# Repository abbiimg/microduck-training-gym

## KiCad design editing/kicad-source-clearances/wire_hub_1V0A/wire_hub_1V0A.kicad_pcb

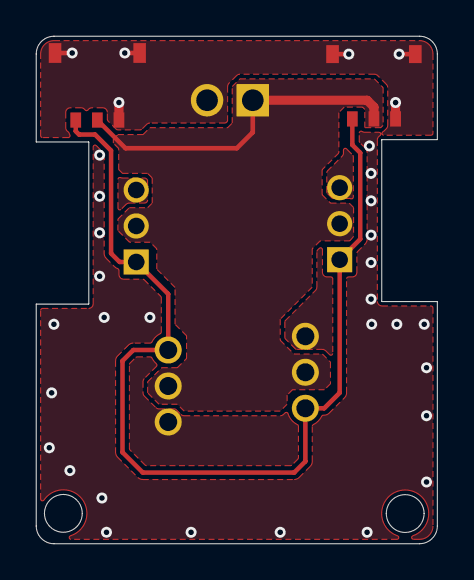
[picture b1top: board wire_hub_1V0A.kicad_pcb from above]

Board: 2 copper layers, 22.3 x 28.2 mm, 7 parts (0 on the bottom side), 3 nets.

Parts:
CN1: DB125-2.54-2P-GN-S; CN1
J1: HC-1.2-3PWT; J1
J2: BM03B-ACHSS-GAN-ETF(LF)(SN); J2
J3: A2007WR-3P; J3
J4: A2007WR-3P; J4
J5: A2007WV-3P; J5
J6: A2007WV-3P; J6

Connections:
/Battery: CN1.1, J1.2, J2.2, J3.2, J4.2, J5.2, J6.2
/DXL_BUS: J1.3, J2.3, J3.1, J4.1, J5.1, J6.1
/GND: CN1.2, J1.1, J1.4, J1.5, J2.1, J2.4, J2.5, J3.3, J4.3, J5.3, J6.3

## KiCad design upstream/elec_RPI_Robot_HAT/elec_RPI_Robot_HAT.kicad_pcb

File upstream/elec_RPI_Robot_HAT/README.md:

# "RPI_Robot_HAT" Electronic Board

> "RPI_Robot_HAT" is a raspberry pi HAT designed for small/medium size robots. It has an IMU, Dynamixel connectors and audio. Its size fits a Raspberry PI zero.

The RPI_Robot_HAT gathers:

- **IMU** over I2C + data fusion
- **Dynamixel motor communication**: both TTL and 485 to drive Dynamixel/Feetech motor (requires cable adaptation)
- **in/out audio device** with an integrated mems microphone. Wago connectors allows connection of loudspeaker and extra microphone.
- **expension Qwiic connectors**, 1 mm/3V3. Please refer to the schematic for knowing which can be use on you raspberry pi.

The RPI_Robot_HAT can be power from 5 to 28V. It is designed to use of the motor connector as an power input.

## Releases
| Release | Date       | Designer | Check  | Comments                               |
|---------|------------|----------|--------|----------------------------------------|
| A1      | 06/03/2026 | EB       | SN     | Initial drawing                        |
| B1      | 06/05/2026 | EB       | SN     |[fixed] Acc. is at 0x19 I2C address<br />[fixed] Soft reset of the audio DAC<br />[fixed] Ideal diode<br />[fixed] Know position of IMU<br />[update] Dynamixel_dir is based on Tx<br />[added] IMU can be disconnected<br />[added] IMU_IT is cabled<br />[added] Access to I2C0<br />[added] Switch off detection|
| C1      | 08/07/2026 | EB       | SN     | [fix] 3V3 on IO10/11<br />[fix] MOS direction of Ideal diode<br />[update] I2C3 is by default instead of reserved I2C|
| D1      | 06/10/2026 | EB       | Claude | [update] IMU is now LSM6DSV16XTR<br />[update] RS485 Driver<br /> [update] screwable terminals for audio|

## Basically
 - Designed with KiCAD 9.

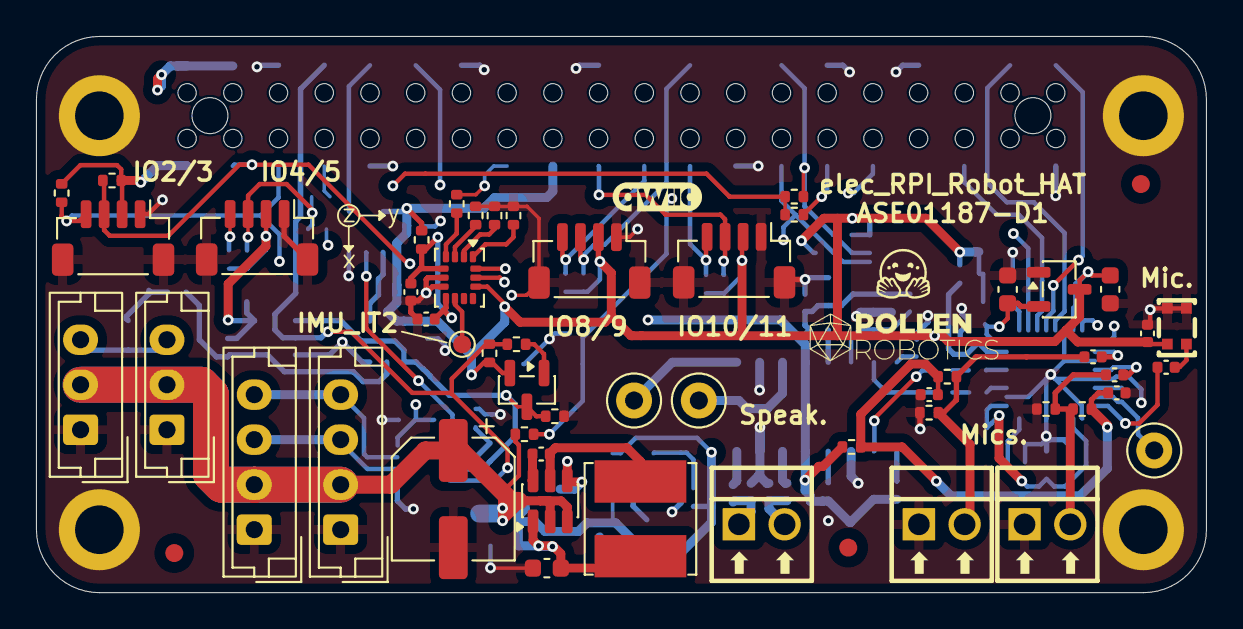
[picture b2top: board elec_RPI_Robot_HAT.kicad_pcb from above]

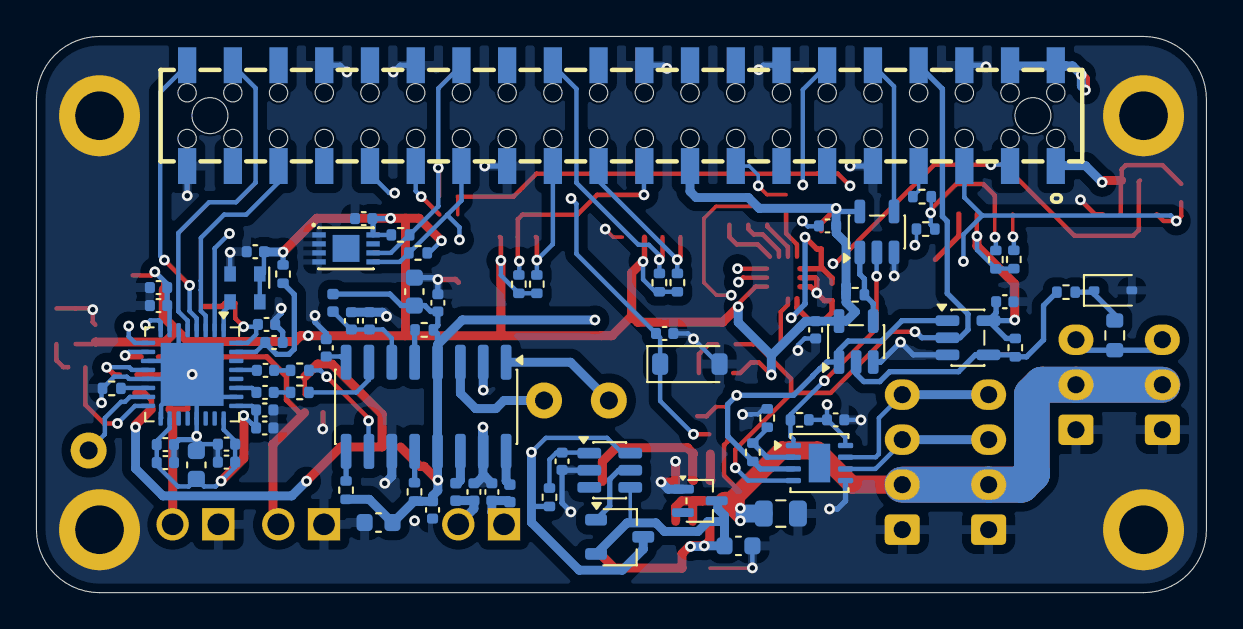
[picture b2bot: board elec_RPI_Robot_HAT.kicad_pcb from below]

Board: 4 copper layers, 65.0 x 30.9 mm, 132 parts (74 on the bottom side), 74 nets.

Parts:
C1, C2, C3, C4, C6, C10, C27, C29, C31, C33, C35, C40, C41, C42, C43: 1u; C_0402_1005Metric
C5, C7, C12, C13, C37: 10u; C_0603_1608Metric
C8, C9: 220n; C_0402_1005Metric
C11, C14, C15, C16, C17, C18, C26, C28, C30, C32, C36, C38: 100n; C_0402_1005Metric
C19: 10u 63V; CP_Elec_6.3x7.7
C20: 100n 50V; C_0402_1005Metric
C21, C22: 22u 6V3; C_0603_1608Metric
C23, C24, C39: 100n 6V3; C_0402_1005Metric
C25: DNP-100n; C_0402_1005Metric
C34, C44: 10n; C_0402_1005Metric
C45: 10u 35V; C_0805_2012Metric
D1: BAT54W; SOT-323_SC-70
D2: 3V3 Zener Diode; D_SOD-123
D4: 5V1; D_SOD-323
FB1: 1.3A 600R@100MHz; L_0402_1005Metric
FB2, FB3: 2A - 120R@100MHz; L_0402_1005Metric
FID1, FID2, FID3: DNP Fiducial; Fiducial_1mm_Mask2mm
G1: qwiic_Logo; Logo_qwiic_5mm
H2: Logo HF 2025; Logo_HF_2025
H3: DNP Logo Pollen 2021; Logo_Pollen_2021_sq
J1, J2, J9: Screw term.; CONN-TH_DB125-2.54-2P-GN
J3, J11: Dynamixel-4; JST_EH_B4B-EH-A_1x04_P2.50mm_Vertical
J4: Female Header 2x20 SMD; PinHeader_2x20_P2.54mm_Vertical_with_rasp_HAT_zero_SMD_conn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
J5, J6, J7, J8: JST SH; JST_SH_BM04B-SRSS-TB_1x04-1MP_P1.00mm_Vertical
J13, J14: Dynamixel-3; JST_EH_B3B-EH-A_1x03_P2.50mm_Vertical
L4: 6,8u 2A; L_Bourns_SRN6045TA
MK1: Microphone_MEMS; MIC-SMD_4P-L2.8-W1.9-P1.84-TL
Q1: MMBT3906; SOT-23
Q2: N-Channel 5A; TSOT-23
R1, R2, R6, R12, R13, R20, R21, R24, R26, R27, R29, R31, R32, R34, R35, R38, R39: 10k; R_0402_1005Metric
R3, R4, R5, R7, R9, R14, R15, R18, R19, R25, R30, R40: 0R; R_0402_1005Metric
R8: 100R; R_0402_1005Metric
R10, R11: DNP-10k; R_0402_1005Metric
R16, R17, R41: DNP-0R; R_0402_1005Metric
R22, R23: 4k7; R_0402_1005Metric
R28: 20k; R_0402_1005Metric
R33: 150R; R_0402_1005Metric
R36, R37: DNP-1M; R_0402_1005Metric
R42: 1k; R_0402_1005Metric
TH1: 100R thermistor; R_0603_1608Metric
TP2, TP3, TP4: TestPoint; TestPoint_Loop_D2.50mm_Drill1.0mm_LowProfile
TP5: TestPoint; TestPoint_Pad_D1.0mm
U1: PAM8406D; SOIC-16_3.9x9.9mm_P1.27mm
U2: TLV320AIC3104IRHBR; VQFN-32-1EP_5x5mm_P0.5mm_EP3.5x3.5mm
U3: XC6206P182MR; SOT-23-3
U4: DNP-CAT24C32HU4; TDFN-8_L3.0-W2.0-P0.50-BL-EP
U5: 74LVC1G08; SOT-23-5
U6: SN74LVC1G125DBV; SOT-23-5
U7: SN74LVC1G126DBVR; SOT-23-5
U8: GM3088ENA; DFN-8-1EP_3x3mm_P0.65mm_EP1.2x2.15mm
U9: AP63205; TSOT-23-6
U10: LM5050-1; TSOT-23-6
U12: LSM6DSV16XTR; LGA-14_3x2.5mm_P0.5mm_LayoutBorder3x4y
Y1: 12 MHz; Oscillator_SMD_Abracon_ASDMB-4Pin_2.5x2.0mm

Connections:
+1V8: C12.1, C26.2, U2.32 (DVDD), U3.2 (VO)
+3V3: C11.2, C13.1, C14.2, C15.2, C16.2, C17.2, C18.2, C25.2, C27.2, C28.2, C29.2, C30.2, C31.2, C32.2, C35.2, C36.2, C37.1, J4.1, J4.17, J5.2, J6.2, J7.2, J8.2, MK1.4 (+), Q1.2 (E), R6.1, R9.2, R10.1, R11.1, R12.1, R13.1, R20.1, R21.1, R26.2, R29.1, R31.1, R32.1, R34.1, R35.1, R38.1, R39.1, U2.7 (IOVDD), U2.18 (DRVDD), U2.24 (DRVDD), U2.25 (AVDD), U3.3 (VI), U4.8 (VCC), U5.5 (VCC), U6.5 (VCC), U7.5 (VCC), U8.8 (VCC), U12.12 (CS), Y1.1 (Tri-State), Y1.4 (VDD)
+5V: C4.1, C5.1, C6.1, C7.1, FB1.2, J4.2, J4.4, Q2.3 (D), R3.2, R4.2, R5.2, R8.1, R42.1, U1.4 (PVDDL), U1.13 (PVDDR), U10.6 (OUT)
+BATT: C19.1, C45.1, J3.2, J11.2, J13.2, J14.2, R24.2, U9.2 (EN), U9.3 (IN)
/Schematic/Audio/ID_SC: J4.28, R10.2, R16.1, U4.6 (SCL)
/Schematic/Audio/ID_SD: J4.27, R11.2, R17.1, U4.5 (SDA)
/Schematic/Audio/IO_02: J4.3, J5.3, R12.2, U2.9 (SDA), U12.14 (SDA)
/Schematic/Audio/IO_03: J4.5, J5.4, R13.2, U2.8 (SCL), U12.13 (SCL)
/Schematic/Audio/IO_04: J4.7, R18.1
/Schematic/Audio/IO_05: J4.29, R19.1
/Schematic/Audio/IO_06: C44.1, D2.1 (K), J4.31, R24.1
/Schematic/Audio/IO_08: J4.24, J7.3, R34.2
/Schematic/Audio/IO_09: J4.21, J7.4, R35.2
/Schematic/Audio/IO_10: J4.19, J8.3, R38.2
/Schematic/Audio/IO_11: J4.23, J8.4, R39.2
/Schematic/Audio/IO_14: J4.8, R26.1, R27.1, U7.2, U8.4 (DI)
/Schematic/Audio/IO_15: J4.10, U5.4
/Schematic/Audio/IO_18: J4.12, U2.2 (BCLK)
/Schematic/Audio/IO_19: J4.35, U2.3 (WCLK)
/Schematic/Audio/IO_20: J4.38, U2.5 (DOUT)
/Schematic/Audio/IO_21: J4.40, U2.4 (DIN)
/Schematic/Audio/IO_22: J4.15, R25.1
/Schematic/Dynamixel/Dynamixel_dir: Q1.3 (C), R28.2, R40.1, U6.1, U7.1, U8.3 (DE)
GND: C3.1, C4.2, C5.2, C6.2, C7.2, C8.2, C9.2, C11.1, C12.2, C13.2, C14.1, C15.1, C16.1, C17.1, C18.1, C19.2, C21.2, C22.2, C23.2, C24.1, C25.1, C26.1, C27.1, C28.1, C29.1, C30.1, C31.1, C32.1, C33.2, C34.2, C35.1, C36.1, C37.2, C38.1, C39.2, C42.1, C43.1, C44.2, C45.2, D1.1 (A), D2.2 (A), D4.2 (A), J2.1, J3.1, J4.6, J4.9, J4.14, J4.20, J4.25, J4.30, J4.34, J4.39, J4.MP (MountPin), J5.1, J5.MP (MountPin), J6.1, J6.MP (MountPin), J7.1, J7.MP (MountPin), J8.1, J8.MP (MountPin), J9.1, J11.1, J13.1, J14.1, MK1.2 (-), MK1.3 (-), R7.1, R14.1, R15.1, R28.1, R30.1, R36.1, R37.1, R41.1, U1.2 (PGNDL), U1.11 (GND), U1.15 (PGNDR), U2.6 (DVSS), U2.11 (MIC1LM/LINE1LM), U2.13 (MIC1RM/LINE1RM), U2.17 (AVSS1), U2.21 (DRVSS), U2.26 (AVSS2), U2.33 (EP), U3.1 (GND), U4.1 (A0), U4.2 (A1), U4.3 (A2), U4.4 (GND), U5.3 (GND), U6.3 (GND), U7.3 (GND), U8.5 (GND), U9.4 (GND), U10.2 (GND), U12.6 (GND), U12.7 (GND), Y1.2 (GND)
unnamed: C1.2, R1.1
unnamed: C2.2, R2.1
unnamed: C10.1, MK1.1 (-)
unnamed: C42.2, C43.2, R22.2, R23.2, R42.2
unnamed: C21.1, C22.1, D1.3 (K), L4.1, Q2.2 (S), U9.1 (FB), U10.4 (IN)
unnamed: D4.1 (K), R33.2, TH1.1
unnamed: C9.1, FB3.2, J1.1
unnamed: C8.1, FB2.2, J1.2
unnamed: C41.2, J2.2, R22.1, R36.2
unnamed: J6.3, R17.2, R18.2, R20.2
unnamed: J6.4, R16.2, R19.2, R21.2
unnamed: C40.2, J9.2, R23.1, R37.2
unnamed: J3.3, J11.3, U8.6 (A)
unnamed: J3.4, J11.4, U8.7 (B)
unnamed: J13.3, J14.3, TH1.2
unnamed: Q1.1 (B), R27.2
unnamed: Q2.1 (G), U10.5 (GATE)
unnamed: R31.2, U5.1, U6.4
unnamed: R32.2, R33.1, U6.2, U7.4
unnamed: TP3.1, U1.1 (+OUT_L)
unnamed: FB3.1, U1.16 (+OUT_R)
unnamed: TP4.1, U1.3 (-OUT_L)
unnamed: FB2.1, U1.14 (-OUT_R)
unnamed: R1.2, U1.7 (INL)
unnamed: R2.2, U1.10 (INR)
unnamed: R5.1, U1.9 (MODE)
unnamed: C33.1, C34.1, FB1.1, U1.6 (VDD)
unnamed: C3.2, U1.8 (VREF)
unnamed: R4.1, U1.5 (~MUTE)
unnamed: R3.1, U1.12 (~SHND)
unnamed: C1.1, U2.27 (LEFT_LOP)
unnamed: U2.1 (MCLK), Y1.3 (OUT)
unnamed: C41.1, U2.10 (MIC1LP/LINE1LP)
unnamed: C40.1, U2.12 (MIC1RP/LINE1RP)
unnamed: R7.2, U2.14 (MIC2L/LINE2L/MICDET)
unnamed: C10.2, U2.16 (MIC2R/LINE2R)
unnamed: TP2.1, U2.15 (MICBIAS)
unnamed: C2.1, U2.29 (RIGHT_LOP)
unnamed: C38.2, R6.2, U2.31 (~RESET)
unnamed: R29.2, U5.2, U8.1 (RO)
unnamed: R40.2, R41.2, U8.2 (~RE)
unnamed: C20.1, U9.6 (BST)
unnamed: C20.2, L4.2, U9.5 (SW)
unnamed: C39.1, R8.2, U10.1 (VS)
unnamed: R25.2, U12.4 (INT1)
unnamed: TP5.1, U12.9 (INT2)
unnamed: R15.2, U12.3 (SCX)
unnamed: R30.2, U12.1 (SDO/SA0)
unnamed: R14.2, U12.2 (SDX)
unnamed: C23.1, C24.2, R9.1, U12.5 (VDDIO), U12.8 (VDD)
